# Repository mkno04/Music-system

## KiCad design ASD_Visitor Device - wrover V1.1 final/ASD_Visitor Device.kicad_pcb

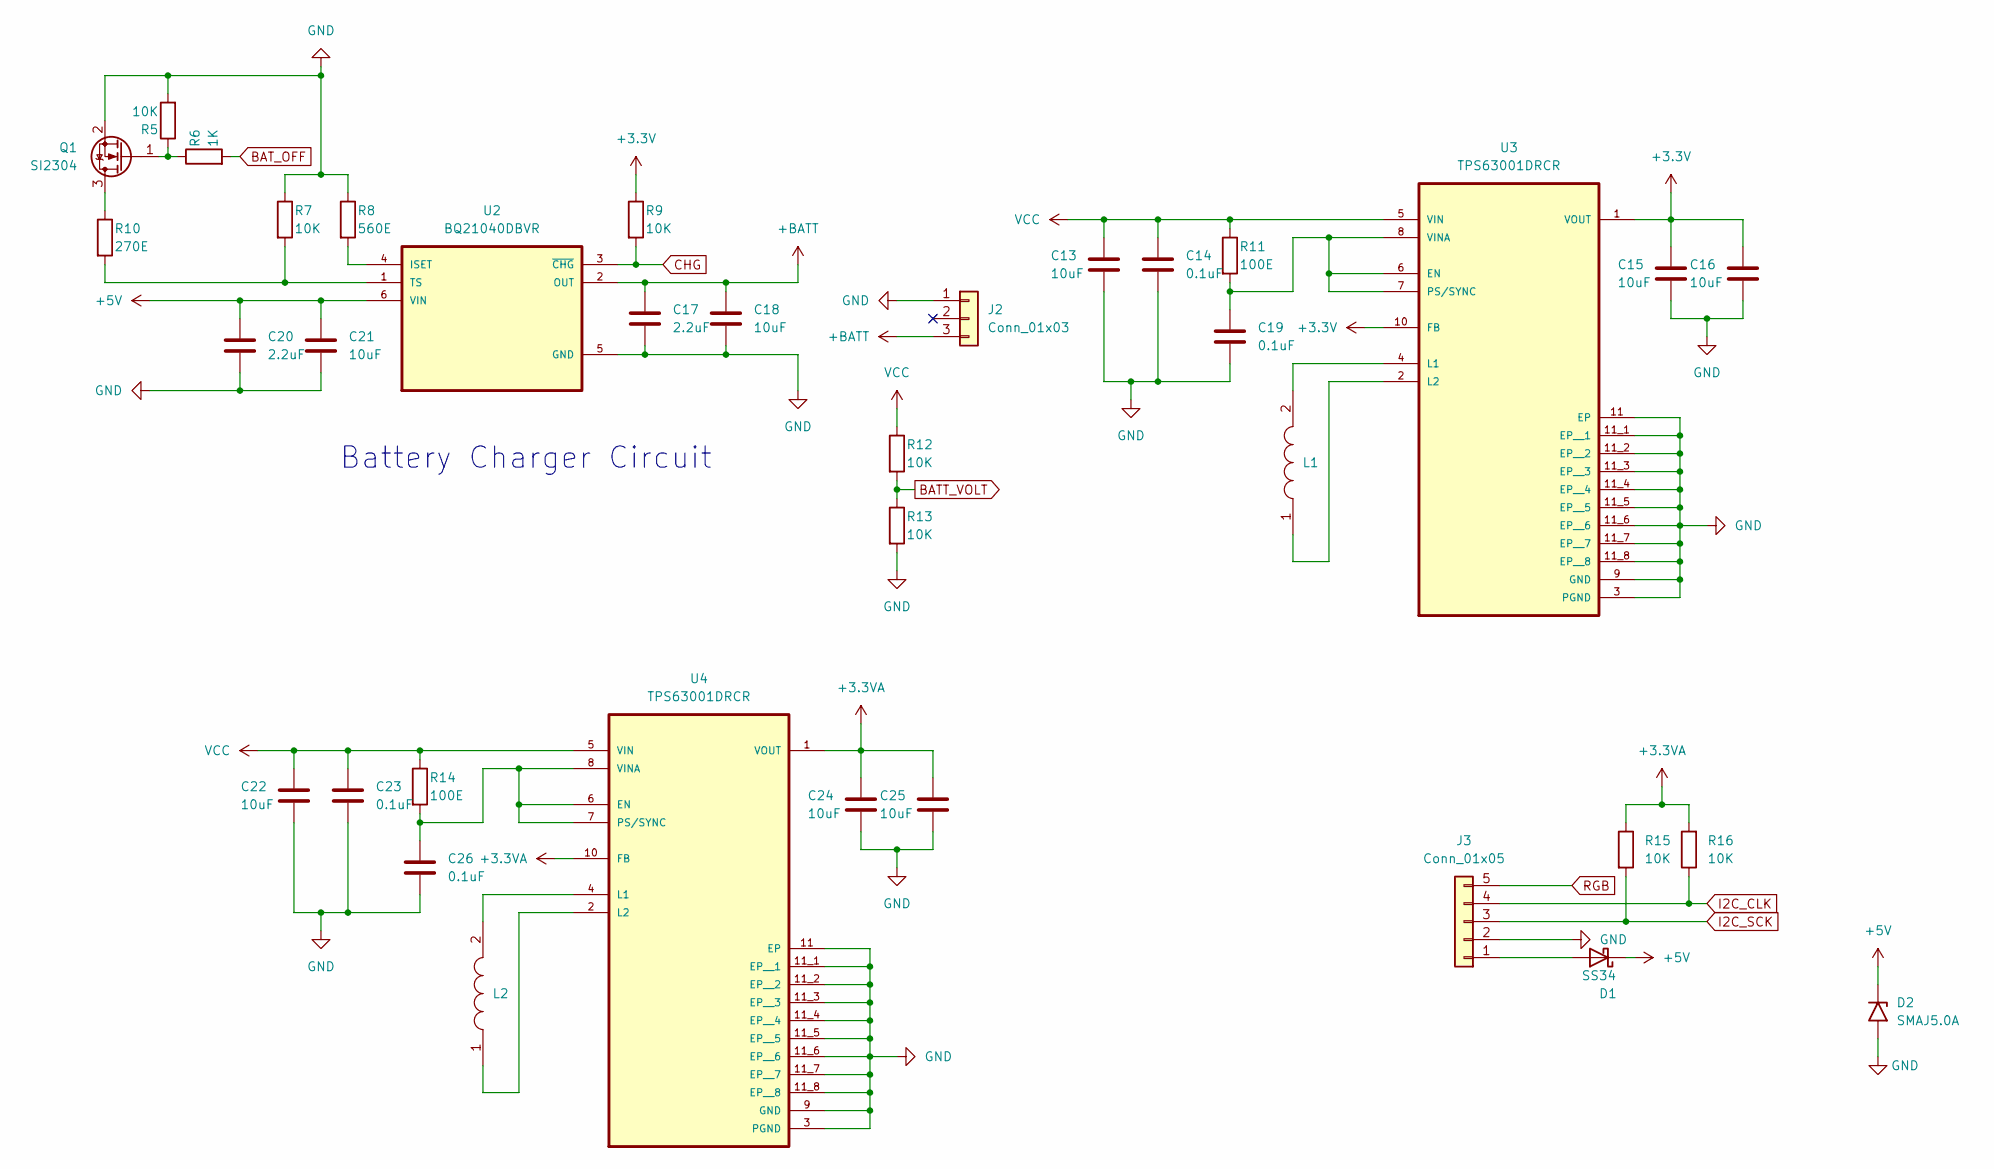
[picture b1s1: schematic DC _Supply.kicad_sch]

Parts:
C13, C15, C16, C18, C21, C22, C24, C25: 10uF; C_0603_1608Metric
C14, C23: 0.1uF; C_0603_1608Metric
C17, C20: 2.2uF; C_0603_1608Metric
C19, C26: 0.1uF; C_0402_1005Metric
D1: SS34; D_SMA
D2: SMAJ5.0A; D_SMA
J2: Conn_01x03; jst 1.25 3 pole
J3: Conn_01x05; JST-5P_1.25mm
L1: SRN8040-100M_INDUC; IND_IHLP-2525CZ-01_VIS-M
L2: 2.2uH; IND_IHLP-2525CZ-01_VIS-M
Q1: SI2304; SOT-23; Part No SI2304DDS-T1-GE3
R5, R7, R9, R12, R13, R15, R16: 10K; R_0402_1005Metric
R6: 1K; R_0402_1005Metric
R8: 560E; R_0402_1005Metric
R10: 270E; R_0402_1005Metric
R11, R14: 100E; R_0402_1005Metric
U2: BQ21040DBVR; SOT-23-6
U3, U4: TPS63001DRCR; TPS63000DRCR; PARTREV OCT 2015

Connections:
+3.3V: C15.1, C16.1, R9.1, U3.1 (VOUT), U3.10 (FB); also elsewhere on the board
+3.3VA: C24.1, C25.1, R15.1, R16.2, U4.1 (VOUT), U4.10 (FB); also elsewhere on the board
+5V: C20.1, C21.1, D1.1 (K), D2.1 (A1), U2.6 (VIN)
+BATT: C17.1, C18.1, J2.3, U2.2 (OUT); also elsewhere on the board
BATT_VOLT: R12.2, R13.1; also elsewhere on the board
BAT_OFF: R6.2; also elsewhere on the board
CHG: R9.2, U2.3 (~CHG); also elsewhere on the board
GND: C13.2, C14.2, C15.2, C16.2, C17.2, C18.2, C19.2, C20.2, C21.2, C22.2, C23.2, C24.2, C25.2, C26.2, D2.2 (A2), J2.1, J3.2, Q1.2 (S), R5.2, R7.1, R8.1, R13.2, U2.5 (GND), U3.3 (PGND), U3.9 (GND), U3.11 (EP), U3.11_1 (EP__1), U3.11_2 (EP__2), U3.11_3 (EP__3), U3.11_4 (EP__4), U3.11_5 (EP__5), U3.11_6 (EP__6), U3.11_7 (EP__7), U3.11_8 (EP__8), U4.3 (PGND), U4.9 (GND), U4.11 (EP), U4.11_1 (EP__1), U4.11_2 (EP__2), U4.11_3 (EP__3), U4.11_4 (EP__4), U4.11_5 (EP__5), U4.11_6 (EP__6), U4.11_7 (EP__7), U4.11_8 (EP__8); also elsewhere on the board
I2C_CLK: J3.4, R16.1; also elsewhere on the board
I2C_SCK: J3.3, R15.2; also elsewhere on the board
unnamed: D1.2 (A), J3.1
unnamed: Q1.3 (D), R10.1
unnamed: Q1.1 (G), R5.1, R6.1
unnamed: R8.2, U2.4 (ISET)
unnamed: R7.2, R10.2, U2.1 (TS)
unnamed: C19.1, R11.2, U3.6 (EN), U3.7 (PS/SYNC), U3.8 (VINA)
unnamed: L1.2, U3.4 (L1)
unnamed: L1.1, U3.2 (L2)
unnamed: C26.1, R14.2, U4.6 (EN), U4.7 (PS/SYNC), U4.8 (VINA)
unnamed: L2.2, U4.4 (L1)
unnamed: L2.1, U4.2 (L2)
RGB: J3.5; also elsewhere on the board
VCC: C13.1, C14.1, C22.1, C23.1, R11.1, R12.1, R14.1, U3.5 (VIN), U4.5 (VIN); also elsewhere on the board

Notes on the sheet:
Battery Charger Circuit

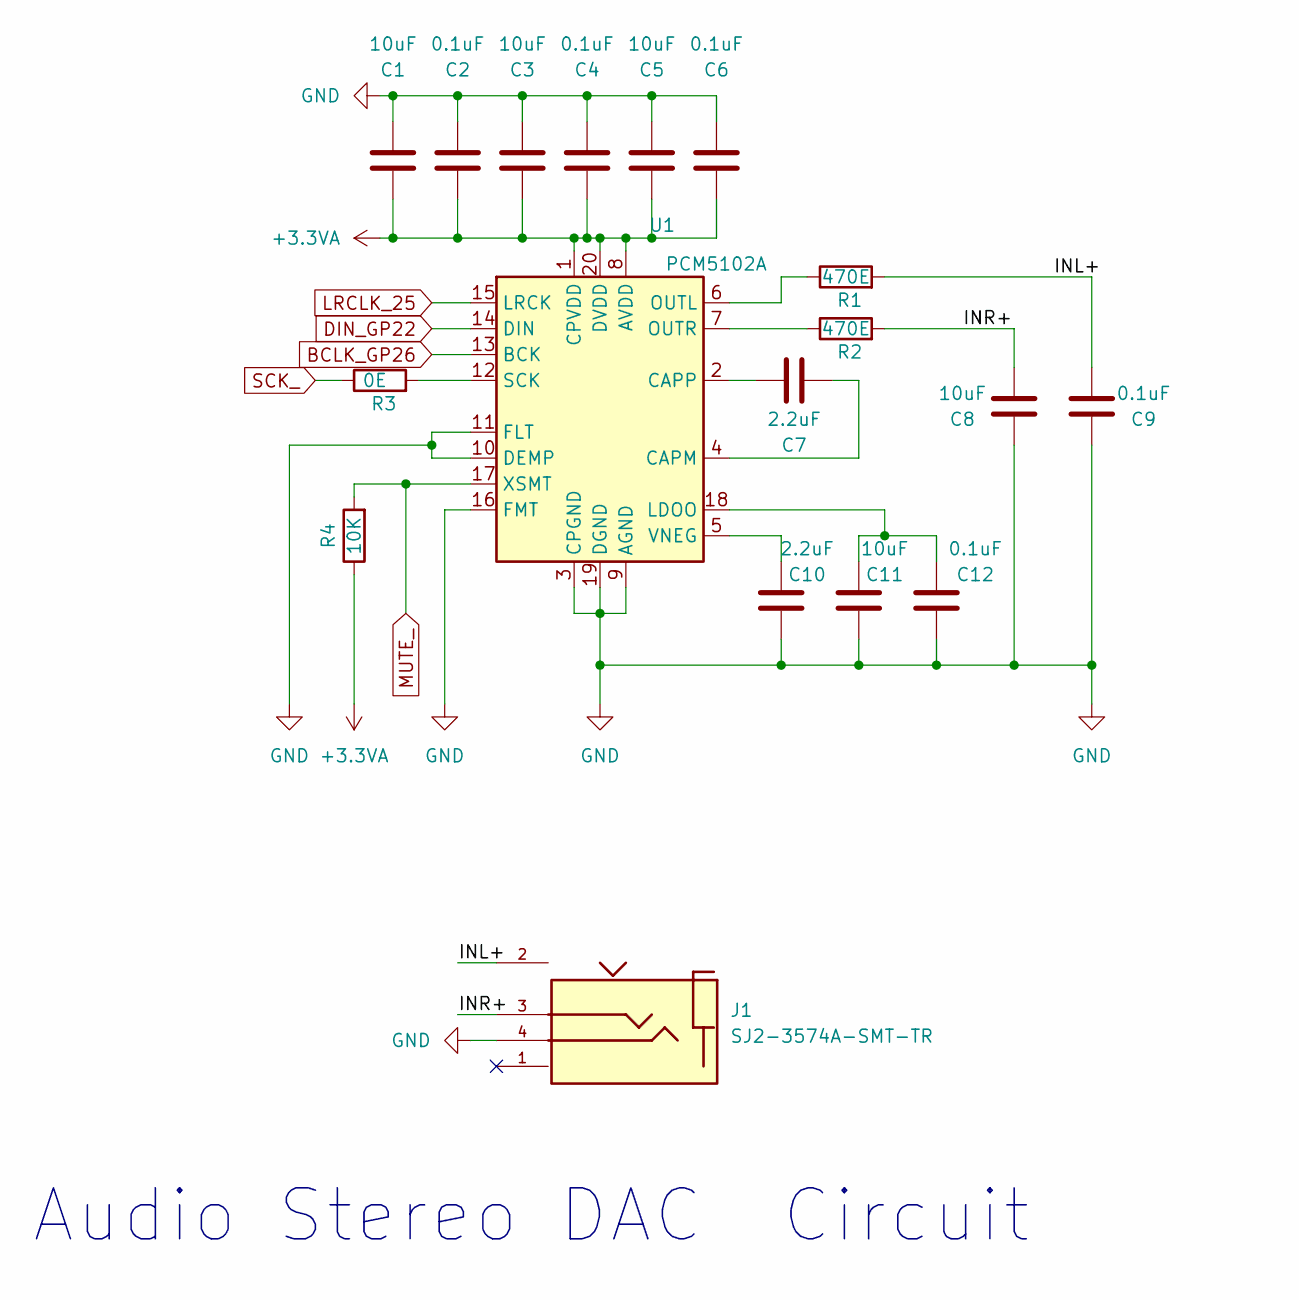
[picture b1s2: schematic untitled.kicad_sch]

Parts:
C1, C3, C5, C8, C11: 10uF; C_0603_1608Metric
C2, C4, C6, C9, C12: 0.1uF; C_0603_1608Metric
C7, C10: 2.2uF; C_0603_1608Metric
J1: SJ2-3574A-SMT-TR; CUI_SJ2-3574A-SMT-TR; PARTREV 1.02
R1, R2: 470E; R_0402_1005Metric
R3: 0E; R_0402_1005Metric
R4: 10K; R_0402_1005Metric
U1: PCM5102A; TSSOP-20_4.4x6.5mm_P0.65mm

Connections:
+3.3VA: C1.1, C2.1, C3.1, C4.1, C5.1, C6.1, R4.1, U1.1 (CPVDD), U1.8 (AVDD), U1.20 (DVDD); also elsewhere on the board
/Audio_Streo/INL+: C9.2, J1.2, R1.2
/Audio_Streo/INR+: C8.2, J1.3, R2.2
BCLK_GP26: U1.13 (BCK); also elsewhere on the board
DIN_GP22: U1.14 (DIN); also elsewhere on the board
GND: C1.2, C2.2, C3.2, C4.2, C5.2, C6.2, C8.1, C9.1, C10.1, C11.1, C12.1, J1.4, U1.3 (CPGND), U1.9 (AGND), U1.10 (DEMP), U1.11 (FLT), U1.16 (FMT), U1.19 (DGND); also elsewhere on the board
LRCLK_25: U1.15 (LRCK); also elsewhere on the board
MUTE_: R4.2, U1.17 (XSMT); also elsewhere on the board
unnamed: C7.1, U1.4 (CAPM)
unnamed: C7.2, U1.2 (CAPP)
unnamed: C11.2, C12.2, U1.18 (LDOO)
unnamed: R1.1, U1.6 (OUTL)
unnamed: R2.1, U1.7 (OUTR)
unnamed: R3.2, U1.12 (SCK)
unnamed: C10.2, U1.5 (VNEG)
SCK_: R3.1

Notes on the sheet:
Audio Stereo DAC Circuit

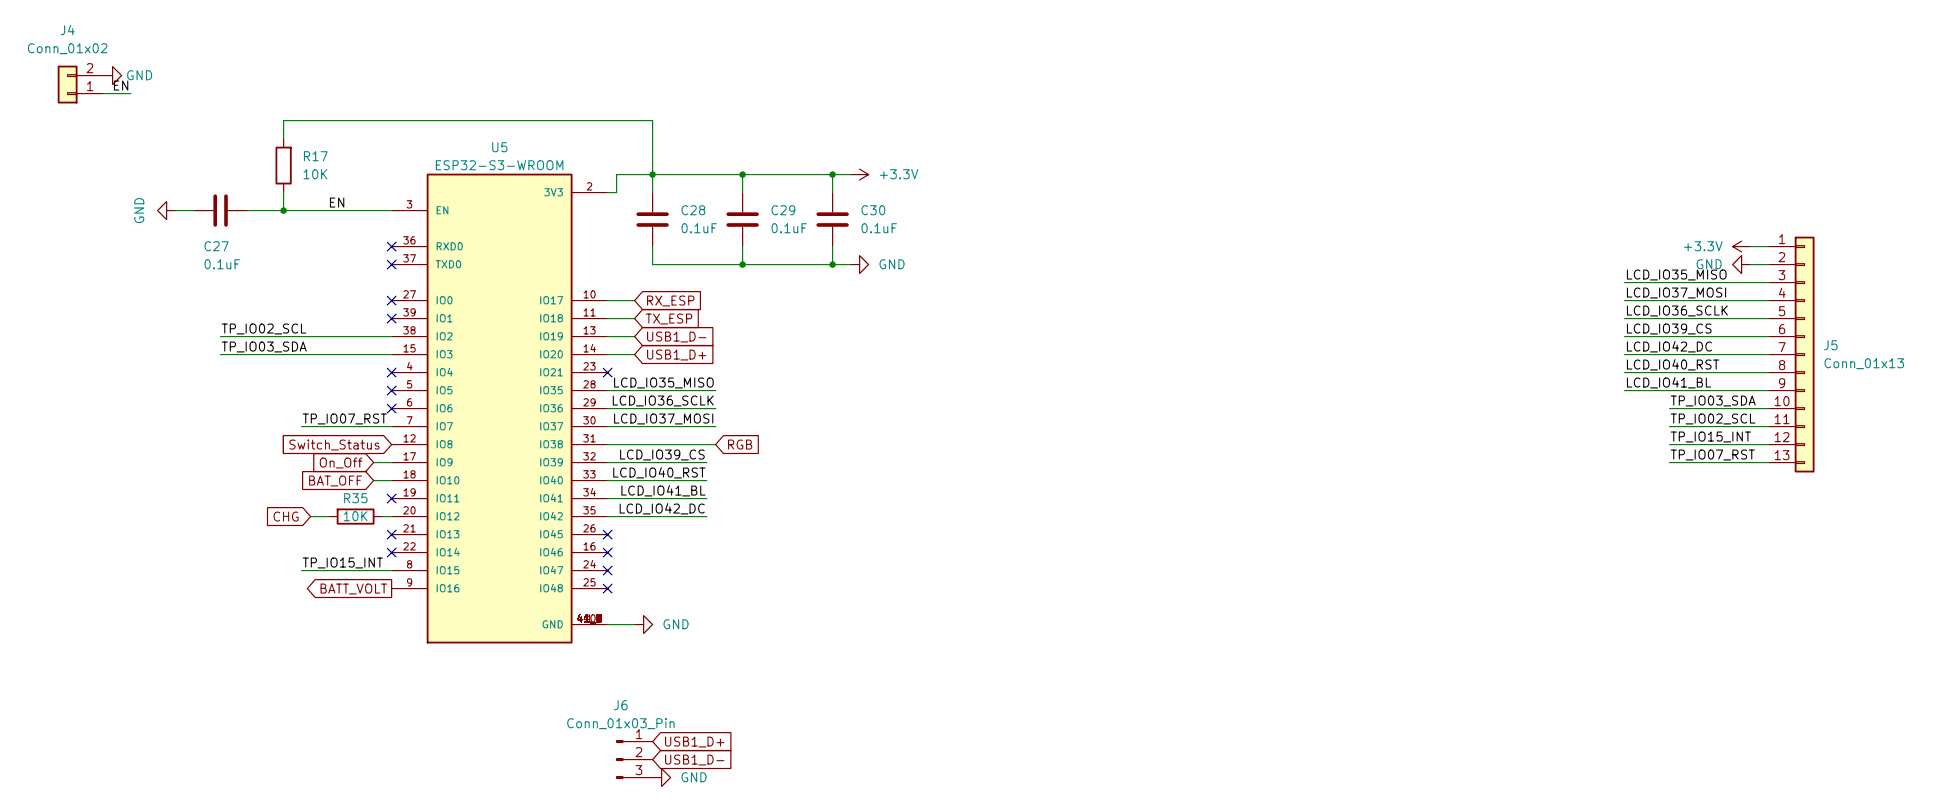
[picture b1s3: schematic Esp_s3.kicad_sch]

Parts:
C27, C28, C29, C30: 0.1uF; C_0603_1608Metric
J4: Conn_01x02; PinHeader_1x02_P1.27mm_Vertical
J5: Conn_01x13; JST_GH_SM13B-GHS-TB_1x13-1MP_P1.25mm_Horizontal
J6: Conn_01x03_Pin; PinHeader_1x03_P2.00mm_Vertical
R17, R35: 10K; R_0402_1005Metric
U5: ESP32-S3-WROOM; ESP32-S3-WROOM1-N4R2; PARTREV v1.0

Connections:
+3.3V: C28.1, C29.1, C30.1, J5.1, R17.2, U5.2 (3V3); also elsewhere on the board
/esp s3/EN: C27.1, J4.1, R17.1, U5.3 (EN)
/esp s3/LCD_IO35_MISO: J5.3, U5.28 (IO35)
/esp s3/LCD_IO36_SCLK: J5.5, U5.29 (IO36)
/esp s3/LCD_IO37_MOSI: J5.4, U5.30 (IO37)
/esp s3/LCD_IO39_CS: J5.6, U5.32 (IO39)
/esp s3/LCD_IO40_RST: J5.8, U5.33 (IO40)
/esp s3/LCD_IO41_BL: J5.9, U5.34 (IO41)
/esp s3/LCD_IO42_DC: J5.7, U5.35 (IO42)
/esp s3/TP_IO02_SCL: J5.11, U5.38 (IO2)
/esp s3/TP_IO03_SDA: J5.10, U5.15 (IO3)
/esp s3/TP_IO07_RST: J5.13, U5.7 (IO7)
/esp s3/TP_IO15_INT: J5.12, U5.8 (IO15)
BATT_VOLT: U5.9 (IO16); also elsewhere on the board
BAT_OFF: U5.18 (IO10); also elsewhere on the board
CHG: R35.2; also elsewhere on the board
GND: C27.2, C28.2, C29.2, C30.2, J4.2, J5.2, J6.3, U5.1 (GND), U5.40 (GND), U5.41_1 (GND), U5.41_2 (GND), U5.41_3 (GND), U5.41_4 (GND), U5.41_5 (GND), U5.41_6 (GND), U5.41_7 (GND), U5.41_8 (GND), U5.41_9 (GND); also elsewhere on the board
unnamed: R35.1, U5.20 (IO12)
On_Off: U5.17 (IO9); also elsewhere on the board
RGB: U5.31 (IO38); also elsewhere on the board
RX_ESP: U5.10 (IO17); also elsewhere on the board
Switch_Status: U5.12 (IO8); also elsewhere on the board
TX_ESP: U5.11 (IO18); also elsewhere on the board
USB1_D+: J6.1, U5.14 (IO20)
USB1_D-: J6.2, U5.13 (IO19)

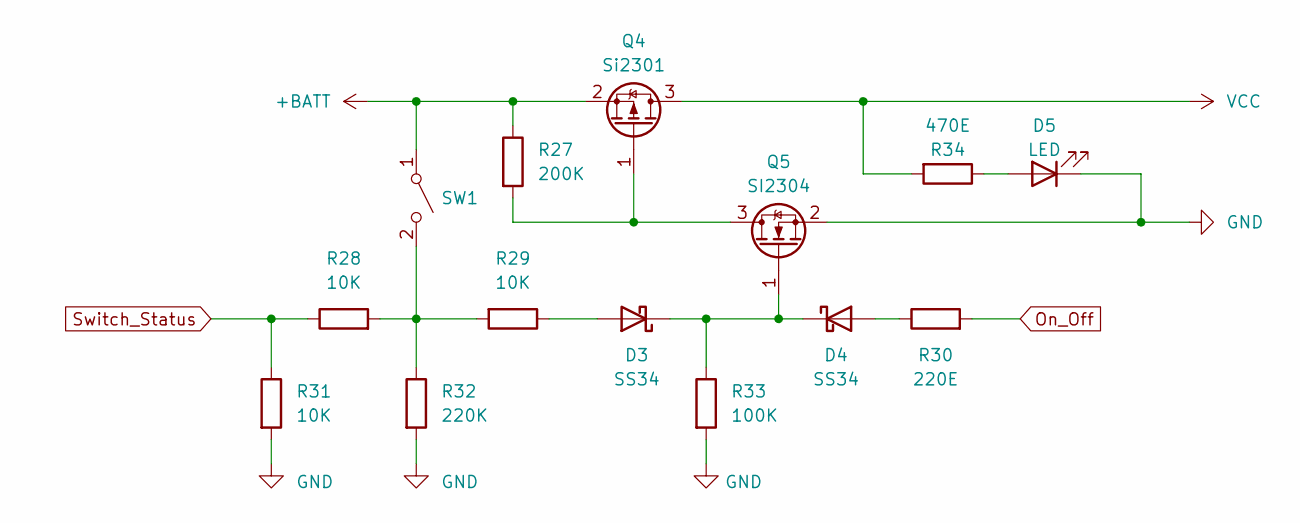
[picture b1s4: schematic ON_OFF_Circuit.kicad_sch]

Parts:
D3, D4: SS34; D_SOD-323
D5: LED; LED_0402_1005Metric
Q4: Si2301; SOT-23
Q5: SI2304; SOT-23
R27: 200K; R_0402_1005Metric
R28, R29, R31: 10K; R_0402_1005Metric
R30: 220E; R_0402_1005Metric
R32: 220K; R_0402_1005Metric
R33: 100K; R_0402_1005Metric
R34: 470E; R_0402_1005Metric
SW1: SW_SPST; 4312560587X6

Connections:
+BATT: Q4.2 (S), R27.1, SW1.1 (A); also elsewhere on the board
GND: D5.1 (K), Q5.2 (S), R31.2, R32.2, R33.2; also elsewhere on the board
unnamed: D3.2 (A), R29.1
unnamed: D3.1 (K), D4.1 (K), Q5.1 (G), R33.1
unnamed: D4.2 (A), R30.1
unnamed: D5.2 (A), R34.1
unnamed: Q4.1 (G), Q5.3 (D), R27.2
unnamed: R28.2, R29.2, R32.1, SW1.2 (B)
On_Off: R30.2; also elsewhere on the board
Switch_Status: R28.1, R31.1; also elsewhere on the board
VCC: Q4.3 (D), R34.2; also elsewhere on the board

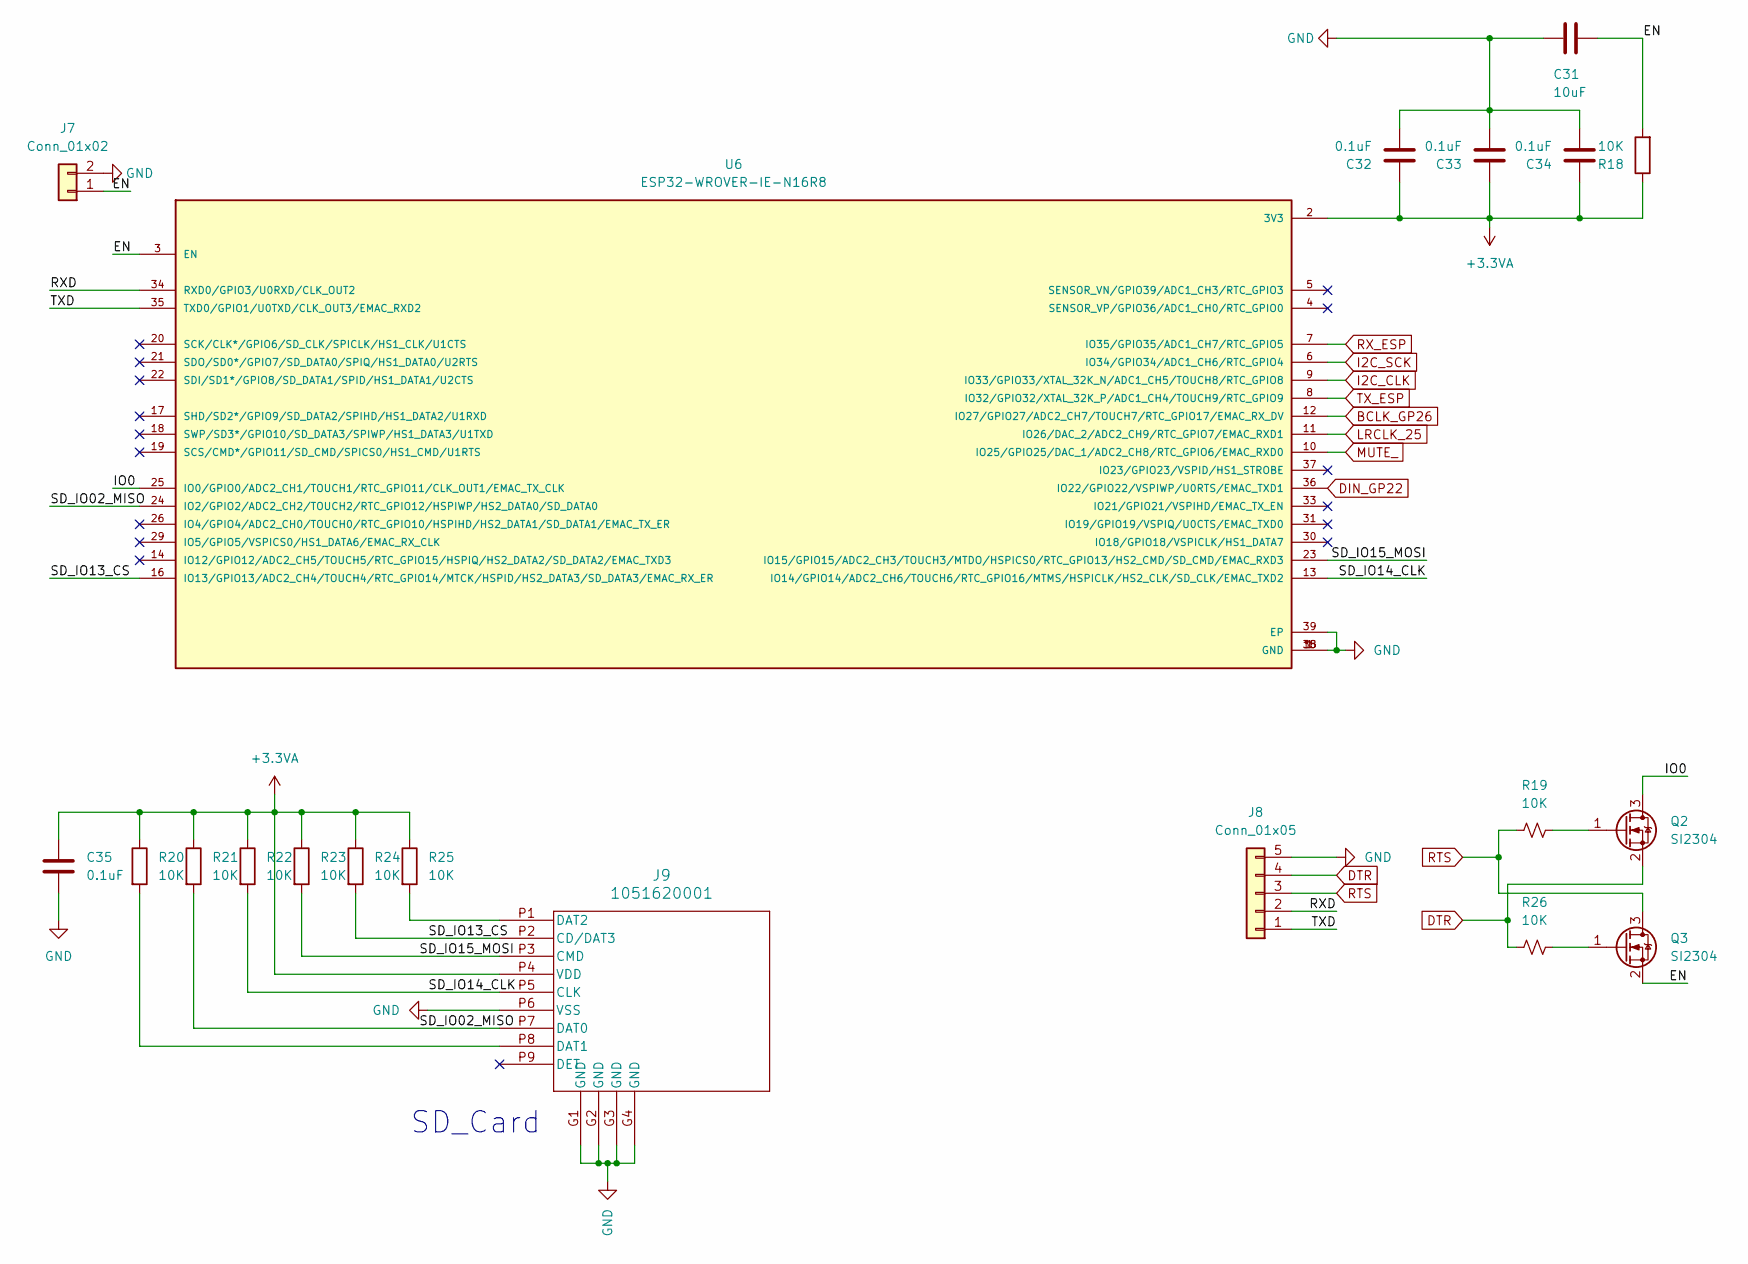
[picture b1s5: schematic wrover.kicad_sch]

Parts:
C31: 10uF; C_0603_1608Metric
C32, C33, C34, C35: 0.1uF; C_0603_1608Metric
J7: Conn_01x02; PinHeader_1x02_P1.27mm_Vertical
J8: Conn_01x05; JST_PH_B5B-PH-K_1x05_P2.00mm_Vertical
J9: 1051620001; 105162-0001_MOL
Q2, Q3: SI2304; SOT-23; Part No SI2304DDS-T1-GE3
R18, R20, R21, R22, R23, R24, R25: 10K; R_0402_1005Metric
R19, R26: 10K; R_0402_1005Metric; Part No RC0603JR-0710KL
U6: ESP32-WROVER-IE-N16R8; XCVR_ESP32-WROVER; PARTREV 2.2

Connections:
+3.3VA: C32.1, C33.1, C34.1, C35.1, J9.P4 (VDD), R18.1, R20.1, R21.1, R22.1, R23.1, R24.1, R25.1, U6.2 (3V3); also elsewhere on the board
/wrover/EN: C31.1, J7.1, Q3.2 (S), R18.2, U6.3 (EN)
/wrover/IO0: Q2.3 (D), U6.25 (IO0/GPIO0/ADC2_CH1/TOUCH1/RTC_GPIO11/CL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)
/wrover/RXD: J8.2, U6.34 (RXD0/GPIO3/U0RXD/CLK_OUT2)
/wrover/SD_IO02_MISO: J9.P7 (DAT0), R21.2, U6.24 (IO2/GPIO2/ADC2_CH2/TOUCH2/RTC_GPIO12/HS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)
/wrover/SD_IO13_CS: J9.P2 (CD/DAT3), R24.2, U6.16 (IO13/GPIO13/ADC2_CH4/TOUCH4/RTC_GPIO14/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)
/wrover/SD_IO14_CLK: J9.P5 (CLK), R22.2, U6.13 (IO14/GPIO14/ADC2_CH6/TOUCH6/RTC_GPIO16/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)
/wrover/SD_IO15_MOSI: J9.P3 (CMD), R23.2, U6.23 (IO15/GPIO15/ADC2_CH3/TOUCH3/MTDO/HSPICS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)
/wrover/TXD: J8.1, U6.35 (TXD0/GPIO1/U0TXD/CLK_OUT3/EMAC_RXD2)
BCLK_GP26: U6.12 (IO27/GPIO27/ADC2_CH7/TOUCH7/RTC_GPIO17/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); also elsewhere on the board
DIN_GP22: U6.36 (IO22/GPIO22/VSPIWP/U0RTS/EMAC_TXD1); also elsewhere on the board
DTR: J8.4, Q2.2 (S), R26.1
GND: C31.2, C32.2, C33.2, C34.2, C35.2, J7.2, J8.5, J9.G1 (GND), J9.G2 (GND), J9.G3 (GND), J9.G4 (GND), J9.P6 (VSS), U6.1 (GND), U6.15 (GND), U6.38 (GND), U6.39 (EP); also elsewhere on the board
I2C_CLK: U6.9 (IO33/GPIO33/XTAL_32K_N/ADC1_CH5/TOUCH8/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); also elsewhere on the board
I2C_SCK: U6.6 (IO34/GPIO34/ADC1_CH6/RTC_GPIO4); also elsewhere on the board
LRCLK_25: U6.11 (IO26/DAC_2/ADC2_CH9/RTC_GPIO7/EMAC_RXD1); also elsewhere on the board
MUTE_: U6.10 (IO25/GPIO25/DAC_1/ADC2_CH8/RTC_GPIO6/EM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); also elsewhere on the board
unnamed: J9.P8 (DAT1), R20.2
unnamed: J9.P1 (DAT2), R25.2
unnamed: Q2.1 (G), R19.2
unnamed: Q3.1 (G), R26.2
RTS: J8.3, Q3.3 (D), R19.1
RX_ESP: U6.7 (IO35/GPIO35/ADC1_CH7/RTC_GPIO5); also elsewhere on the board
TX_ESP: U6.8 (IO32/GPIO32/XTAL_32K_P/ADC1_CH4/TOUCH9/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); also elsewhere on the board

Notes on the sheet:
SD_Card

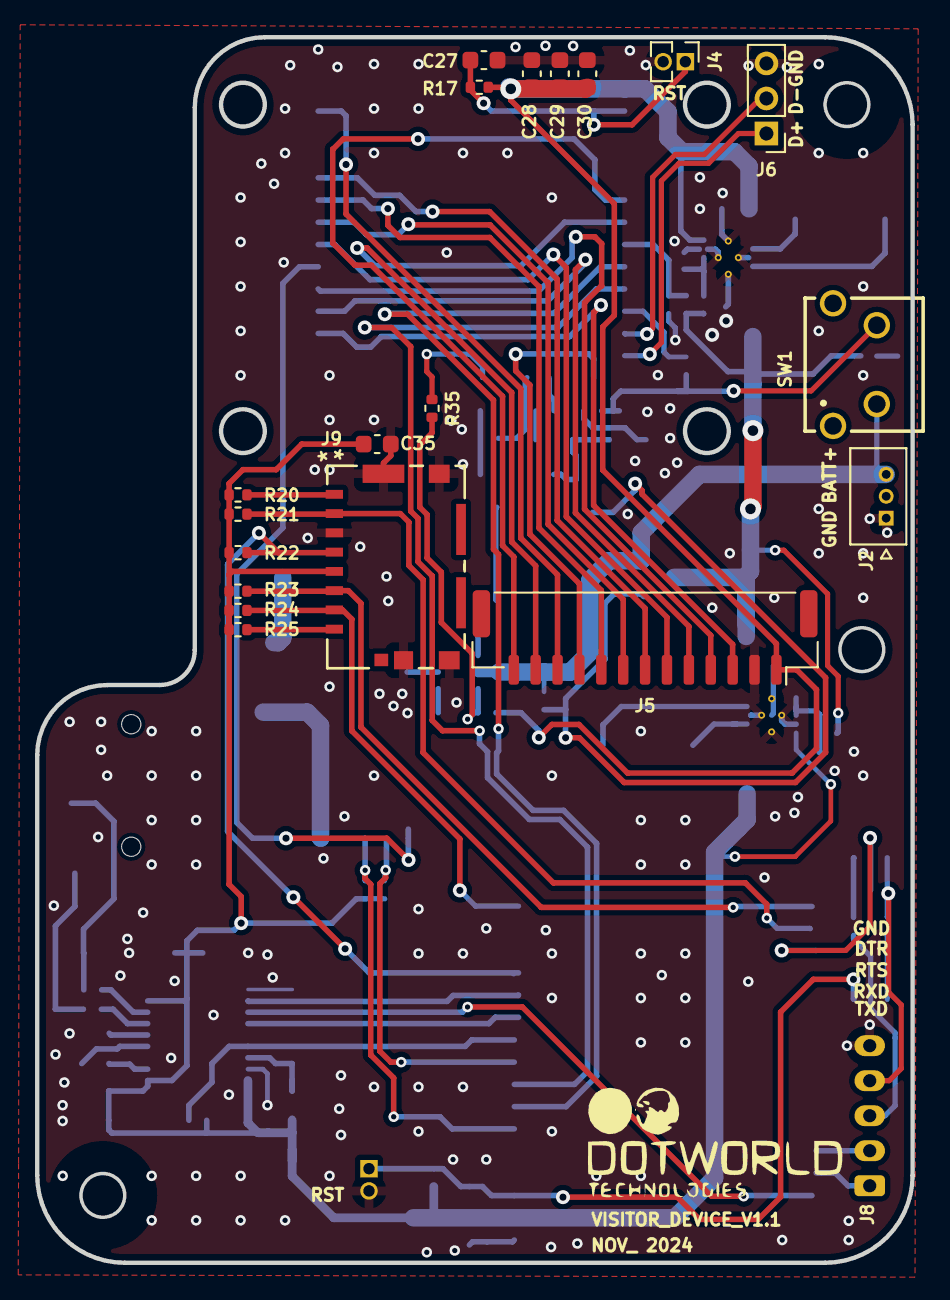
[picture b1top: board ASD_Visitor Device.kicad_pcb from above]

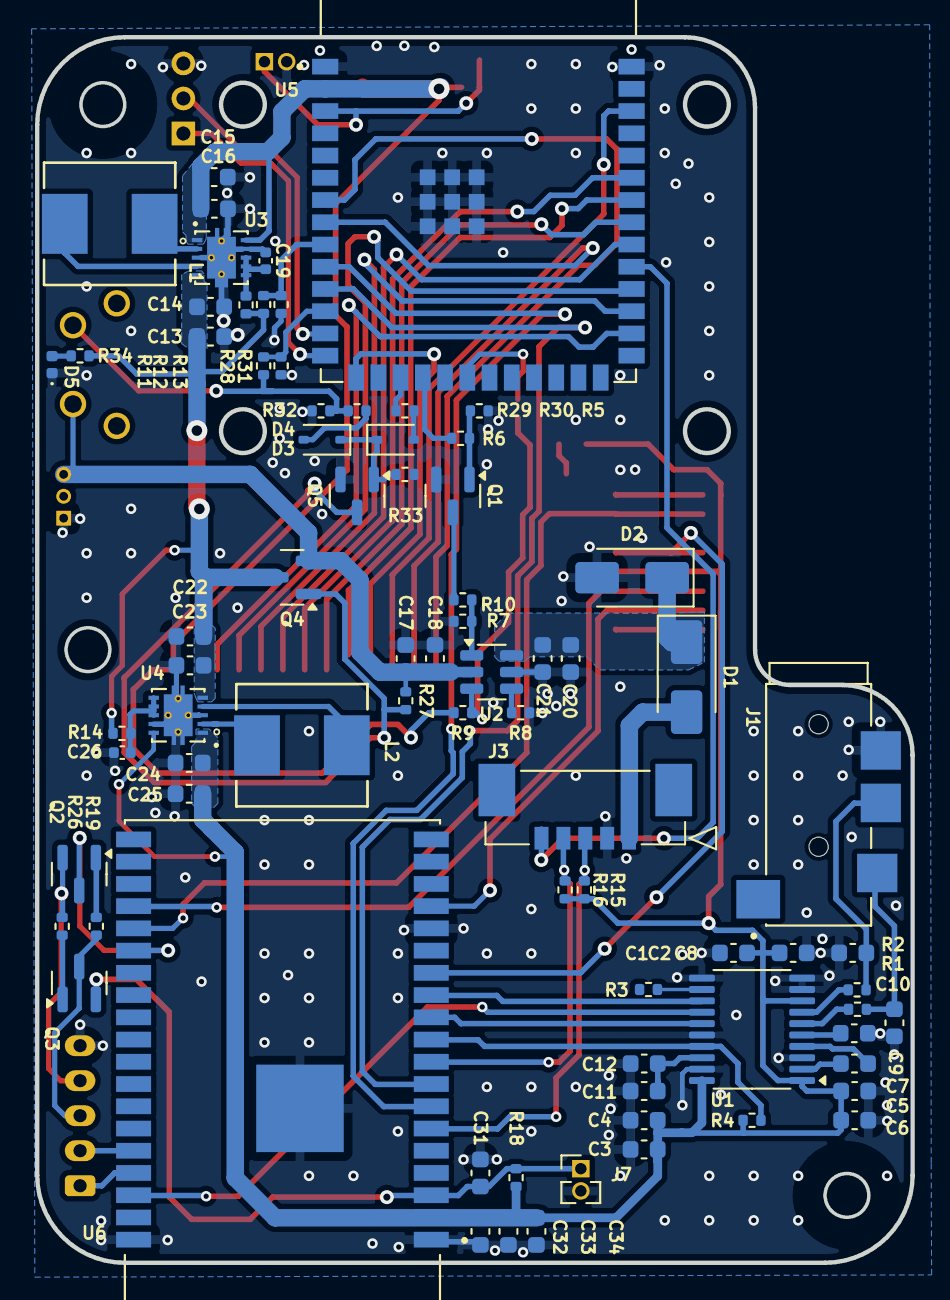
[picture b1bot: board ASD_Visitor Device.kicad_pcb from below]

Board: 2 copper layers, 50.0 x 70.0 mm, 98 parts (78 on the bottom side), 75 nets.

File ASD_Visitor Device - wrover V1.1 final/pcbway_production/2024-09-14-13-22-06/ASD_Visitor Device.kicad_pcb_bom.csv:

Designator,Quantity,Value,Description,Link,Mount_type
"C1, C11, C13, C15, C16, C18, C21, C22, C24, C25, C3, C31, C5, C8",14,10uF,C_0603_1608Metric,,smt
"C10, C17, C20, C7",4,2.2uF,C_0603_1608Metric,,smt
"C12, C14, C2, C23, C27, C28, C29, C30, C32, C33, C34, C35, C4, C6, C9",15,0.1uF,C_0603_1608Metric,,smt
"C19, C26",2,0.1uF,C_0402_1005Metric,,smt
D1,1,SS34,D_SMA,,smt
D2,1,SMAJ5.0A,D_SMA,,smt
"D3, D4",2,1N4148,D_SOD-323,,smt
D5,1,RED LED,LED_0402_1005Metric,,smt
J1,1,SJ2-3574A-SMT-TR,"3.50mm (0.141"", 1/8"", Mini Plug) - Headphone Phone Jack Stereo",,smt
J2,1,Conn_01x03,3 pin JST 1.25mm Through Hole Header Vertical Straight,,tht
J5,1,Conn_01x13,JST_GH_SM13B-GHS-TB_1x13-1MP_P1.25mm_Horizontal,,smt
J8,1,Conn_01x05,JST_PH_B5B-PH-K_1x05_P2.00mm_Vertical,,tht
J9,1,1051620001,Memory Card Connectors 1.45H MICRO SD HEADER WITH D/C PIN ,mouser,smt
"L1, L2",2,SRN8040-100M_INDUCwaveshare,2.2uH (2R2) - 10A - SMD ASPI-0630LR-2R2 Inductor,,smt
"Q1, Q2, Q3, Q5",4,SI2304,SI2304 A4SHB SOT23 N-CH MOSFET,,smt
Q4,1,Si2301,SI2301 A1SHB SOT23 P-CH MOSFET,,smt
"R1, R2, R34",3,470E,R_0402_1005Metric,,smt
R10,1,270E,R_0402_1005Metric,,smt
"R11, R14",2,100E,R_0402_1005Metric,,smt
"R12, R13, R15, R16, R17, R18, R19, R20, R21, R22, R23, R24, R25, R26, R28, R29, R31, R35, R4, R5, R7, R9",22,10K,R_0402_1005Metric,,smt
R27,1,200K,R_0402_1005Metric,,smt
R3,1,0E,R_0402_1005Metric,,smt
R30,1,220E,R_0402_1005Metric,,smt
R32,1,220K,R_0402_1005Metric,,smt
R33,1,100K,R_0402_1005Metric,,smt
R6,1,1K,R_0402_1005Metric,,smt
R8,1,560E,R_0402_1005Metric,,smt
SW1,1,Tactile Switches WS-TATU Tact Switch,,mouser,tht
U1,1,PCM5102A,TSSOP-20_4.4x6.5mm_P0.65mm,,smt
U2,1,BQ21040DBVR,SOT-23-6,,smt
"U3, U4",2,TPS63001DRCR,TPS63001,,smt
U5,1,ESP32-S3-WROOM,ESP32-S3-WROOM1-N4R2,,smt
U6,1,XCVR_ESP32-WROVER,ESP32-WROVER-IE-N16R8 ,,smt
Display,1,,1.28inch Touch LCD,waveshare,
SD Card,1,,sandisk ultra 32gb,,

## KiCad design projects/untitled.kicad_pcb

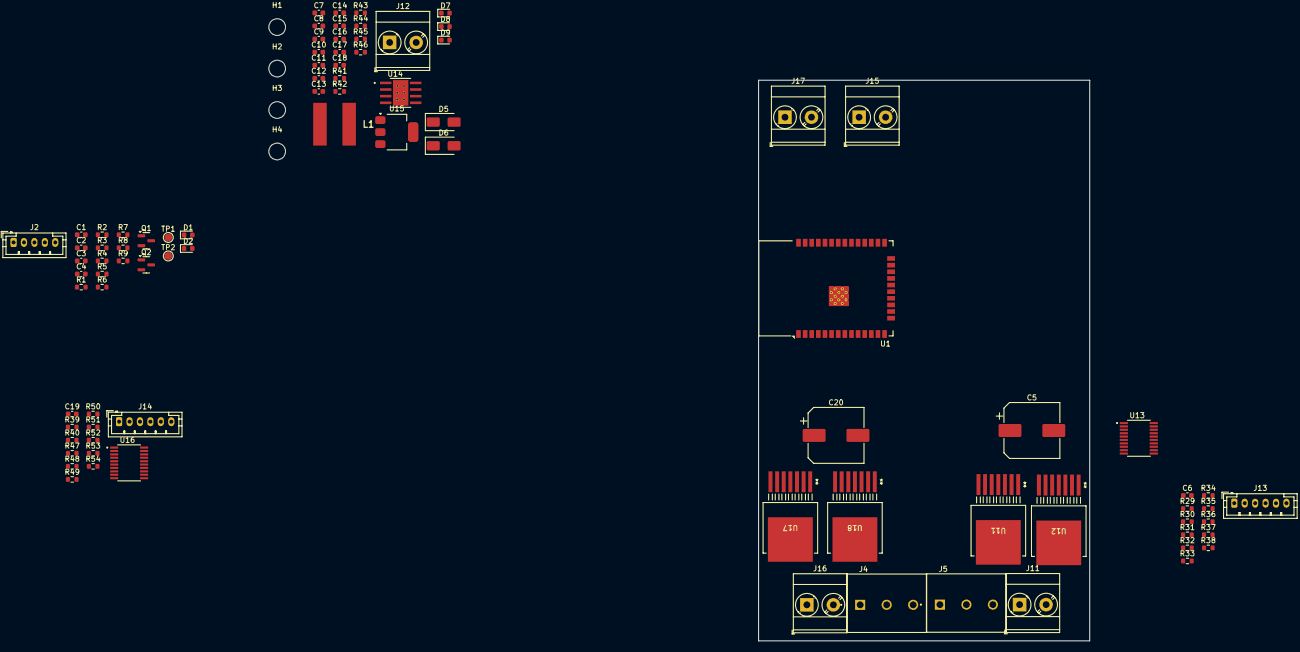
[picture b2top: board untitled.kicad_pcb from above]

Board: 2 copper layers, 63.5 x 107.5 mm, 90 parts (0 on the bottom side), 61 nets, no tracks yet.

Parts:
C1, C2, C3, C6, C7, C16, C18, C19: 0.1uF; C_0603_1608Metric
C4, C15, C17: 10uF; C_0603_1608Metric
C5, C20: 220uF; CP_Elec_10x10.5
C8, C9: 100uF; C_0603_1608Metric
C10: 390pF; C_0603_1608Metric
C11, C12: 22uF; C_0603_1608Metric
C13: 68uF; C_0603_1608Metric
C14: 47nF; C_0603_1608Metric
D1, D2, D7, D8, D9: LED; LED_0603_1608Metric
D5, D6: SS36; D_SMA
H1, H2, H3, H4: MountingHole; MountingHole_3.2mm_M3
J2: Conn_01x05; JST_PH_B5B-PH-K_1x05_P2.00mm_Vertical
J4, J5: Conn_01x03; PHOENIX_1711738
J11, J12, J15, J16, J17: Screw_Terminal_01x02; TerminalBlock_Phoenix_MKDS-3-2-5.08_1x02_P5.08mm_Horizontal
J13, J14: Conn_01x06; JST_PH_B6B-PH-K_1x06_P2.00mm_Vertical
L1: 6.8uH; SRN8040100M_INDUC
Q1, Q2: SI2304; SOT-23
R1, R6, R7, R43: 10K; R_0603_1608Metric
R2, R3, R31, R32, R33, R34, R35, R36, R37, R38, R39, R41, R46, R47, R48, R49, R50, R51, R52, R54: 1K; R_0603_1608Metric
R4, R5, R8, R9, R29, R30, R40, R53: 0E; R_0603_1608Metric
R42: 68K; R_0603_1608Metric
R44: 47K; R_0603_1608Metric
R45: 12K; R_0603_1608Metric
TP1, TP2: TestPoint; TestPoint_Pad_D1.5mm
U1: ESP32-WROOM-32D
U11, U12, U17, U18: IFX007TAUMA1; PG-TO263-7-1_INF-M
U13, U16: SN74HC244PWR; SN74HC244pwr
U14: LMR16030PDDA
U15: AMS1117-3.3; SOT-223-3_TabPin2

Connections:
10: TP1.1, U1.24 (IO2)
11: TP2.1, U1.26 (IO4)
+3.3V: C1.1, C2.1, C3.1, C6.1, C17.1, C18.1, C19.1, J4.1, J5.1, J13.1, J14.1, R1.1, R46.1, U1.2 (VDD), U13.20 (VCC), U15.2 (VO), U16.20 (VCC)
+5V: C10.2, C11.1, C12.1, C13.1, C15.1, C16.1, L1.2, R42.1, R43.1, U15.3 (VI)
+24V: D5.2 (A), J12.2
/Converter Circuits/V_FB: C10.1, R42.2, R45.1, U14.5 (FB)
/EN: C4.1, Q2.2 (S), R1.2, U1.3 (EN)
/IO0: Q1.3 (D), U1.25 (IO0)
/Motor Driver1/HIN_H: U11.3 (INH), U13.16 (1Y2)
/Motor Driver1/HIN_L: U11.2 (IN), U13.18 (1Y1)
/Motor Driver1/LIN_H: U12.3 (INH), U13.12 (1Y4)
/Motor Driver1/LIN_L: U12.2 (IN), U13.14 (1Y3)
/Motor Driver2/HIN_H: U16.16 (1Y2), U17.3 (INH)
/Motor Driver2/HIN_L: U16.18 (1Y1), U17.2 (IN)
/Motor Driver2/LIN_H: U16.12 (1Y4), U18.3 (INH)
/Motor Driver2/LIN_L: U16.14 (1Y3), U18.2 (IN)
/RXD: J2.1, R3.1, U1.34 (RXD0/IO3)
/TXD: J2.2, R2.1, U1.35 (TXD0/IO1)
DTR: J2.4, Q1.2 (S), R7.1
GND: C1.2, C2.2, C3.2, C4.2, C5.2, C6.2, C8.2, C9.2, C11.2, C12.2, C13.2, C14.2, C15.2, C16.2, C17.2, C18.2, C19.2, C20.2, D1.1 (K), D2.1 (K), D6.2 (A), D7.1 (K), D8.1 (K), D9.1 (K), J2.5, J4.3, J5.3, J12.1, J13.6, J14.6, J15.2, J17.2, R31.2, R32.2, R33.2, R34.2, R35.2, R36.2, R37.2, R38.2, R39.2, R44.2, R45.2, R47.2, R48.2, R49.2, R50.2, R51.2, R52.2, R54.2, U1.1 (GND), U1.15 (GND), U1.38 (GND), U1.39 (GND), U11.1 (GND), U12.1 (GND), U13.1 (1~OE), U13.10 (GND), U13.11 (2A1), U13.13 (2A2), U13.15 (2A3), U13.17 (2A4), U13.19 (2~OE), U14.7 (GND), U14.9 (THERMALPAD), U15.1 (GND), U16.1 (1~OE), U16.10 (GND), U16.11 (2A1), U16.13 (2A2), U16.15 (2A3), U16.17 (2A4), U16.19 (2~OE), U17.1 (GND), U18.1 (GND)
H_IS: R5.2, R30.1, R31.1, U11.6 (IS)
H_IS1: R9.2, R50.1, R53.1, U17.6 (IS)
LPWM: J13.4, R36.1, U1.29 (IO5), U13.6 (1A3)
LPWM1: J14.4, R47.1, U1.14 (IO12), U16.6 (1A3)
L_EN: R29.1, R35.1, U1.27 (IO16), U13.8 (1A4)
L_EN1: R39.1, R40.1, U1.28 (IO17), U16.8 (1A4)
L_IS: J13.5, R30.2, R34.1, U1.36 (IO22), U12.6 (IS)
L_IS1: J14.5, R53.2, R54.1, U1.37 (IO23), U18.6 (IS)
unnamed: D1.2 (A), R2.2
unnamed: D2.2 (A), R3.2
unnamed: C8.1, C9.1, D5.1 (K), R41.1, U14.2 (VIN), U14.3 (EN)
unnamed: C7.2, D6.1 (K), L1.1, U14.8 (SW)
unnamed: D7.2 (A), R41.2
unnamed: D8.2 (A), R43.2
unnamed: D9.2 (A), R46.2
unnamed: J11.1, U11.4 (OUT), U11.8 (OUT)
unnamed: J11.2, U12.4 (OUT), U12.8 (OUT)
unnamed: C5.1, J15.1, U11.7 (VS), U12.7 (VS)
unnamed: J16.1, U17.4 (OUT), U17.8 (OUT)
unnamed: J16.2, U18.4 (OUT), U18.8 (OUT)
unnamed: C20.1, J17.1, U17.7 (VS), U18.7 (VS)
unnamed: Q1.1 (G), R6.2
unnamed: Q2.1 (G), R7.2
unnamed: R8.1, U1.30 (IO18)
unnamed: R4.1, U1.31 (IO19)
unnamed: R5.1, U1.10 (IO25)
unnamed: R9.1, U1.11 (IO26)
unnamed: R32.1, U11.5 (SR)
unnamed: R33.1, U12.5 (SR)
unnamed: C7.1, U14.1 (BOOT)
unnamed: R44.1, U14.4 (RT/SYNC)
unnamed: C14.1, U14.6 (SSORPGOOD)
unnamed: R51.1, U17.5 (SR)
unnamed: R52.1, U18.5 (SR)
POT: J5.2, U1.8 (IO32)
POT1: J4.2, U1.9 (IO33)
RPWM: J13.2, R38.1, U1.16 (IO13), U13.2 (1A1)
RPWM1: J14.2, R49.1, U1.13 (IO14), U16.2 (1A1)
RTS: J2.3, Q2.3 (D), R6.1
R_EN: J13.3, R8.2, R29.2, R37.1, U13.4 (1A2)
R_EN1: J14.3, R4.2, R40.2, R48.1, U16.4 (1A2)
